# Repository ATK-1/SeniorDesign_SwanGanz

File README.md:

# Swan Ganz Interface

### Introduction

The contributors to this senior design project were Nathan DeLaRosa, Ashton Knecht, Jack Son, and Jerry Xia under the supervision of Dr. Jonathan Valvano.

This project aims to create a custom, low-cost interface for a Swan-Ganz heart catheter, bypassing the need for expensive cardiac output computers. The catheters intended to be interfaced are the *part number needed* produced by Edwards Lifescience. These catheters interface the *part number needed* pressure transducer, also made by Edwards Lifescience.

The project is split into three sections: the interface hardware, MSPM0 firmware, and the desktop application software. Details about each of these sections can be found in their distinct README files.

[Hardware README(In Progresss)](https://github.com/ATK-1/SeniorDesign_SwanGanz/blob/main/hardware/README.md)

[Firmware README(Requires Development)](https://github.com/ATK-1/SeniorDesign_SwanGanz/blob/main/firmware/README.md)

[Software README(Requires Development)](https://github.com/ATK-1/SeniorDesign_SwanGanz/blob/main/SwanGanzApp/README.md)

### Testing and Verification
*todo*

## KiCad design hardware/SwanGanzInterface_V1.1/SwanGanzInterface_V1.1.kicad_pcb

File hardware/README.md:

# Swan-Ganz Interface Hardware 
The Swan-Ganz Interface Hardware had the following requirements:
- One temperature channel for cardiac output calculation
- Two pressure transducer channels
- Discrete processor
- Intuitive user interface
- Uart to USB converter

The Swan-Ganz Interface has gone through two revisions in development. The first of these circuit boards aimed to have baseline functionality for testing, utilizing a launchpad processor for simplicity. The second revision aimed to refine the original with a discrete processor, a resistive touch screen, audio output, and an integrated UART-to-USB converter. This document will cover the hardware relevant to the second revision circuit board.

## Analog Interface Circuits
The heart of the hardware of this project is the analog interfaces for temperature and pressure. These interfaces are intended to interface the thermistor within the Swan-Ganz catheter and an external pressure transducer. These channels have very similar amplifier architectures; however, the interfaces to the transducers themselves have small differences. Each of the analog input stages was sampled by the analog to digital converters on the MSPM0+ microcontroller.

### Pressure Analog Interface
The Swan-Ganz Catheter does not natively have any pressure transducers. Instead, it has two ports that connect to the fluid in the catheter to external pressure transducers to measure pressure. Thus, to satisfy both pressure ports, two pressure channels must be included to service two independent transducers.

The independent pressure transducers are implemented with a strain gauge. This means that pressure is exerted on wires within the gauge, stretching and compressing them, changing their resistance. The model of the transducer's structure is shown below. The model consists of four variable resistors. Two of the resistors’ resistances are directly proportional to pressure, and two resistors are indirectly proportional. This results in a structure resembling a voltage divider, where a voltage is applied across the transducer; one output lead increases its output voltage with pressure, while the other decreases. 

With this architecture in mind, when a known voltage is applied across the gauge, an output voltage corresponding with pressure is produced across the V+ and V- nodes of the gauge. This signal is supplied to the instrumentation amplifier in the amplifier circuit at a very high gain to produce a clean pressure signal.

### Thermistor Analog Interface
The temperature channel hardware was created to interface with the thermistor embedded at the end of the Swan-Ganz catheter. This thermistor is intended to assist in the calculation of volumetric flow by analyzing its temperature over time; thus, it must translate temperature into a digital value. 

Within the thermistor, temperature and resistance are non-linear and inversely proportional. The thermistor has low resistance when the temperature is high and high resistance when the temperature is low. This relationship is shown by the graph below.

Thus, the thermistor can be placed into a resistor divider with a constant resistance value, producing an output voltage that correlates temperature to output voltage. Despite the relationship between resistance and temperature being non-linear, putting the thermistor in a resistor divider linearizes the output voltage as the relationship between resistance and voltage is non-linear in the divider itself. A second resistor divider with constant resistances is used to set a minimum resistance or a maximum temperature cutoff. The voltage across the variable and constant dividers is inserted into the instrumentation amplifier of the amplifier circuit to finish the temperature-to-voltage conversion. A diagram of the basic temperature circuit is shown below.

### Amplifier Stage
After converting the physical measurement to an analog voltage, the signal still requires analog filtering and amplification prior to being digitally sampled by the microcontroller. To do this, we must know some information about the characteristics of our signals and digital sampling for the design of our amplifier stage.

For our project, we decided to sample both the temperature and pressure signals at 200Hz. The typical resting heart rate in adults ranges from 60 to 100 beats per minute (BPM), which corresponds with a frequency of 1 to 1.67 Hz. During exercise, heart rate can increase up to 170 BPM, which is equivalent to 2.83 Hz. This means that the base frequency we would be investigating for pressure would be around 2 Hz. Despite this, we wanted to be able to view any additional high-frequency components of the heartbeat, as well as oversample our signal to increase the frequency before we started having aliasing in our digital signal. For the temperature component of our interface, we expected to receive even lower frequency signals, having frequencies of at most 10Hz; thus, the 200Hz sample rate was kept for consistency.

Because of the digital sample rate of 200Hz, any noise introduced to the system above 100 Hz cannot be distinguished from our desired signal, and cannot be
digitally filtered. Thus, to ensure that our resulting digital signals do not have any high-frequency noise, we created a 2-pole low-pass Butterworth filter set with a cut-off frequency of 75Hz. This allows us to pass the 20Hz signal frequencies while attenuating any high-frequency noise that is introduced from our environment. 

Amplification in this case is important as it determines the range and resolution of our
measurement. Our microcontroller, the MSPM0+, has 12-bit ADCs with an input voltage range of 0-3.3V. Therefore, to maximize the resolution of our signals, we must amplify the analog signals to make the largest desired analog signal equal to 3.3V. To do this, we have the amplification of the instrumentation amplifiers, tuned by a gain resistor, added by the 2-pole Butterworth filter, and an additional non-inverting amplifier for any additional required gain. To allow for both high resolution and high range, we sample with our ADCs both before and after the additional amplifier, allowing for a low-gain measurement that optimizes for range and a high-gain measurement for resolution. Below are pictures of the full analog input stages for the pressure and temperature interfaces.

## User Interface
The user interface for the Swan-Ganz Interface revolves around the 5” TFT display. This display is controlled by a discrete driver board, the Adafruit 1590. This driver board has SPI communication with the MSPM0+ processor. The driver board is required to boost the input voltage to the screen to 24V, as well as continuously refresh the TFT display. Drivers to communicate with the 1590 were provided by Adafruit and translated to C and to be compatible with the MSPM0+ by Nathan DeLaRosa.

The TFT screen supports a resistive touchscreen. This is provided by four screen outputs that interface with a discrete resistive touch screen controller IC, the TSC2046IPWR. This IC interfaces with the MSPM0+ through SPI and, upon its request, applies a voltage across the screen in the X and Y directions and samples its ADCs to determine the position of a touch to the screen. This information is then transmitted back to the MSPM0+ over another SPI channel for interpretation. The drivers to communicate with the TSC2046IPWR were written by Ashton Knecht.

In the case that issues arise with the resistive touch screen, five discrete hardware buttons are on the PCB as a backup user interface. The TFT is to provide a high-resolution, dynamic user interface able to display both measurement information and user instructions. This allows medical professionals to actively analyze measurement data while maintaining the correct procedure by following directions.

Since MSPM0+ does not natively support USB communication, a discrete UART-to-USB
converter is included to allow the microcontroller to communicate with a host computer running the desktop application. This IC is the FT232RNL, and supports a 3MHz baud rate, and has transmit and receive debug LEDs. Additionally, the manufacturer, FTDI, provides free drivers for Windows, Linux, and macOS.  

Lastly, support for an audio amplifier circuit was made to add a layer of user feedback; however, development on the core functionality and testing were prioritized, and so firmware functionality was not created. 

## Additional Elements of the PCB

### Reverse Polarity Protection

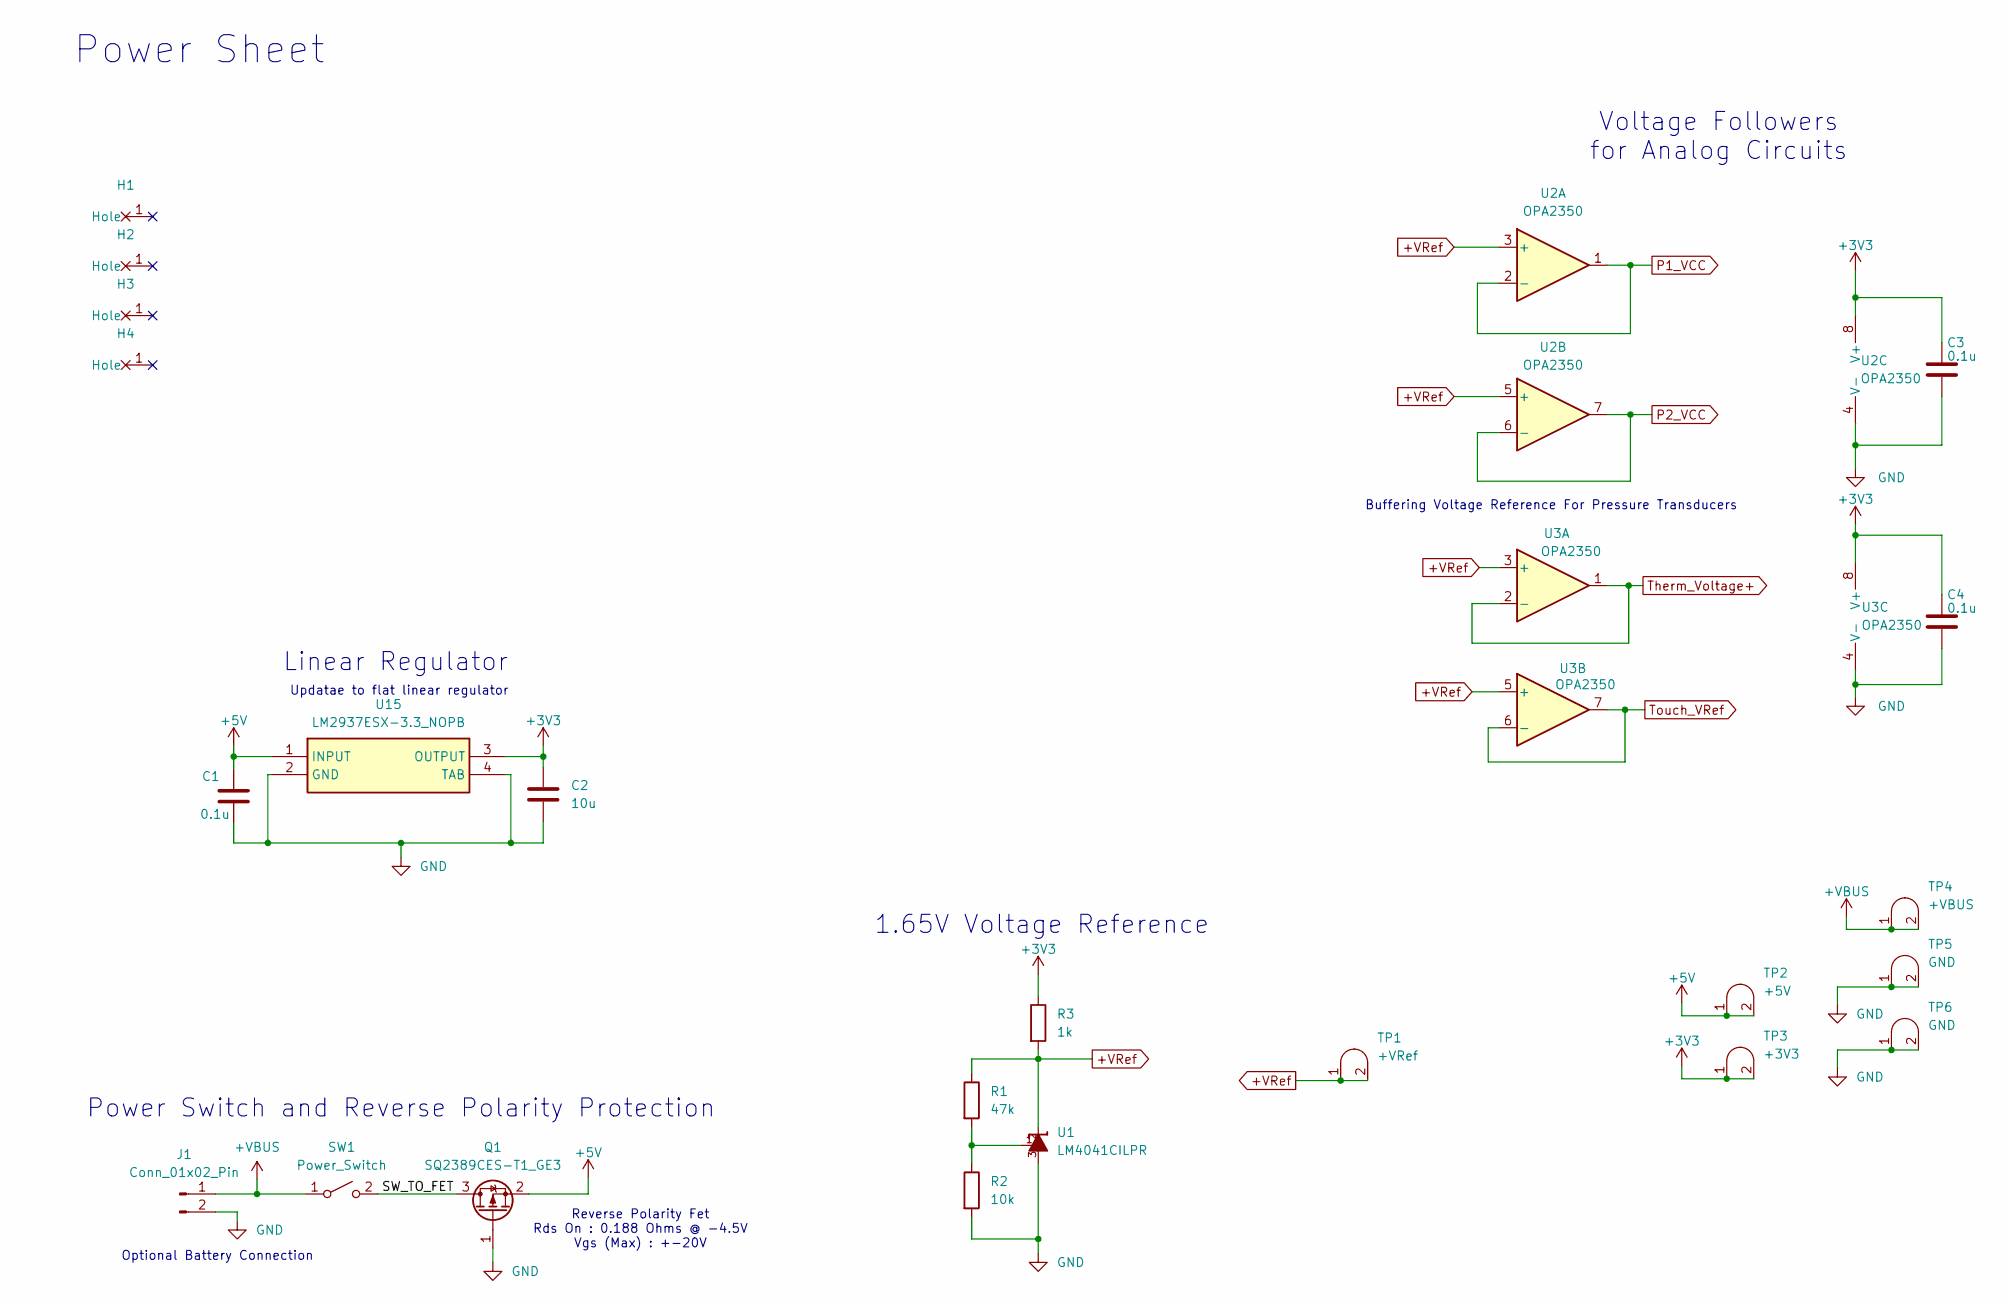
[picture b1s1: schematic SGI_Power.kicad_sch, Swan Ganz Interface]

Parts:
C1, C3, C4: 0.1u; C_0603_1608Metric
C2: 10u; C_1206_3216Metric
H1, H2, H3, H4: MountingHole_4_40
J1: Conn_01x02_Pin; PinHeader_1x02_P2.54mm_Vertical
Q1: SQ2389CES-T1_GE3; SOT-23
R1: 47k; R_0603_1608Metric
R2: 10k; R_0603_1608Metric
R3: 1k; R_0603_1608Metric
SW1: Power_Switch; SW-T3-1A-A-A3-S1
TP1: +VRef; Testpoint_1x02_P2.54mm
TP2: +5V; Testpoint_1x02_P2.54mm
TP3: +3V3; Testpoint_1x02_P2.54mm
TP4: +VBUS; Testpoint_1x02_P2.54mm
TP5, TP6: GND; Testpoint_1x02_P2.54mm
U1: LM4041CILPR; ti_LM4041CILPR
U2, U3: OPA2350; DIP-8_W7.62mm
U15: LM2937ESX-3.3_NOPB; Manufacturer_Part_Number LM2937ESX-3.3/NOPB; Mouser Part Number 926-LM2937ESX33NOPB

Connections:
+3V3: C2.1, C3.1, C4.1, R3.1, TP3.1 (A), TP3.2 (B), U2.8 (V+), U3.8 (V+), U15.3 (OUTPUT); also elsewhere on the board
+5V: C1.1, Q1.2 (S), TP2.1 (A), TP2.2 (B), U15.1 (INPUT); also elsewhere on the board
+VBUS: J1.1, SW1.1 (A), TP4.1 (A), TP4.2 (B); also elsewhere on the board
+VRef: R1.1, R3.2, TP1.1 (A), TP1.2 (B), U1.2, U2.3 (+), U2.5 (+), U3.3 (+), U3.5 (+)
/Power/SW_TO_FET: Q1.3 (D), SW1.2 (B)
GND: C1.2, C2.2, C3.2, C4.2, J1.2, Q1.1 (G), R2.2, TP5.1 (A), TP5.2 (B), TP6.1 (A), TP6.2 (B), U1.3, U2.4 (V-), U3.4 (V-), U15.2 (GND), U15.4 (TAB); also elsewhere on the board
unnamed: R1.2, R2.1, U1.1
P1_VCC: U2.1, U2.2 (-); also elsewhere on the board
P2_VCC: U2.6 (-), U2.7; also elsewhere on the board
Therm_Voltage+: U3.1, U3.2 (-); also elsewhere on the board
Touch_VRef: U3.6 (-), U3.7; also elsewhere on the board

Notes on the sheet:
Buffering Voltage Reference For Pressure Transducers
Power Switch and Reverse Polarity Protection
Power Sheet
Updatae to flat linear regulator
Reverse Polarity Fet Rds On : 0.188 Ohms @ -4.5V Vgs (Max) : +-20V
Voltage Followers for Analog Circuits
Linear Regulator
1.65V Voltage Reference
Optional Battery Connection

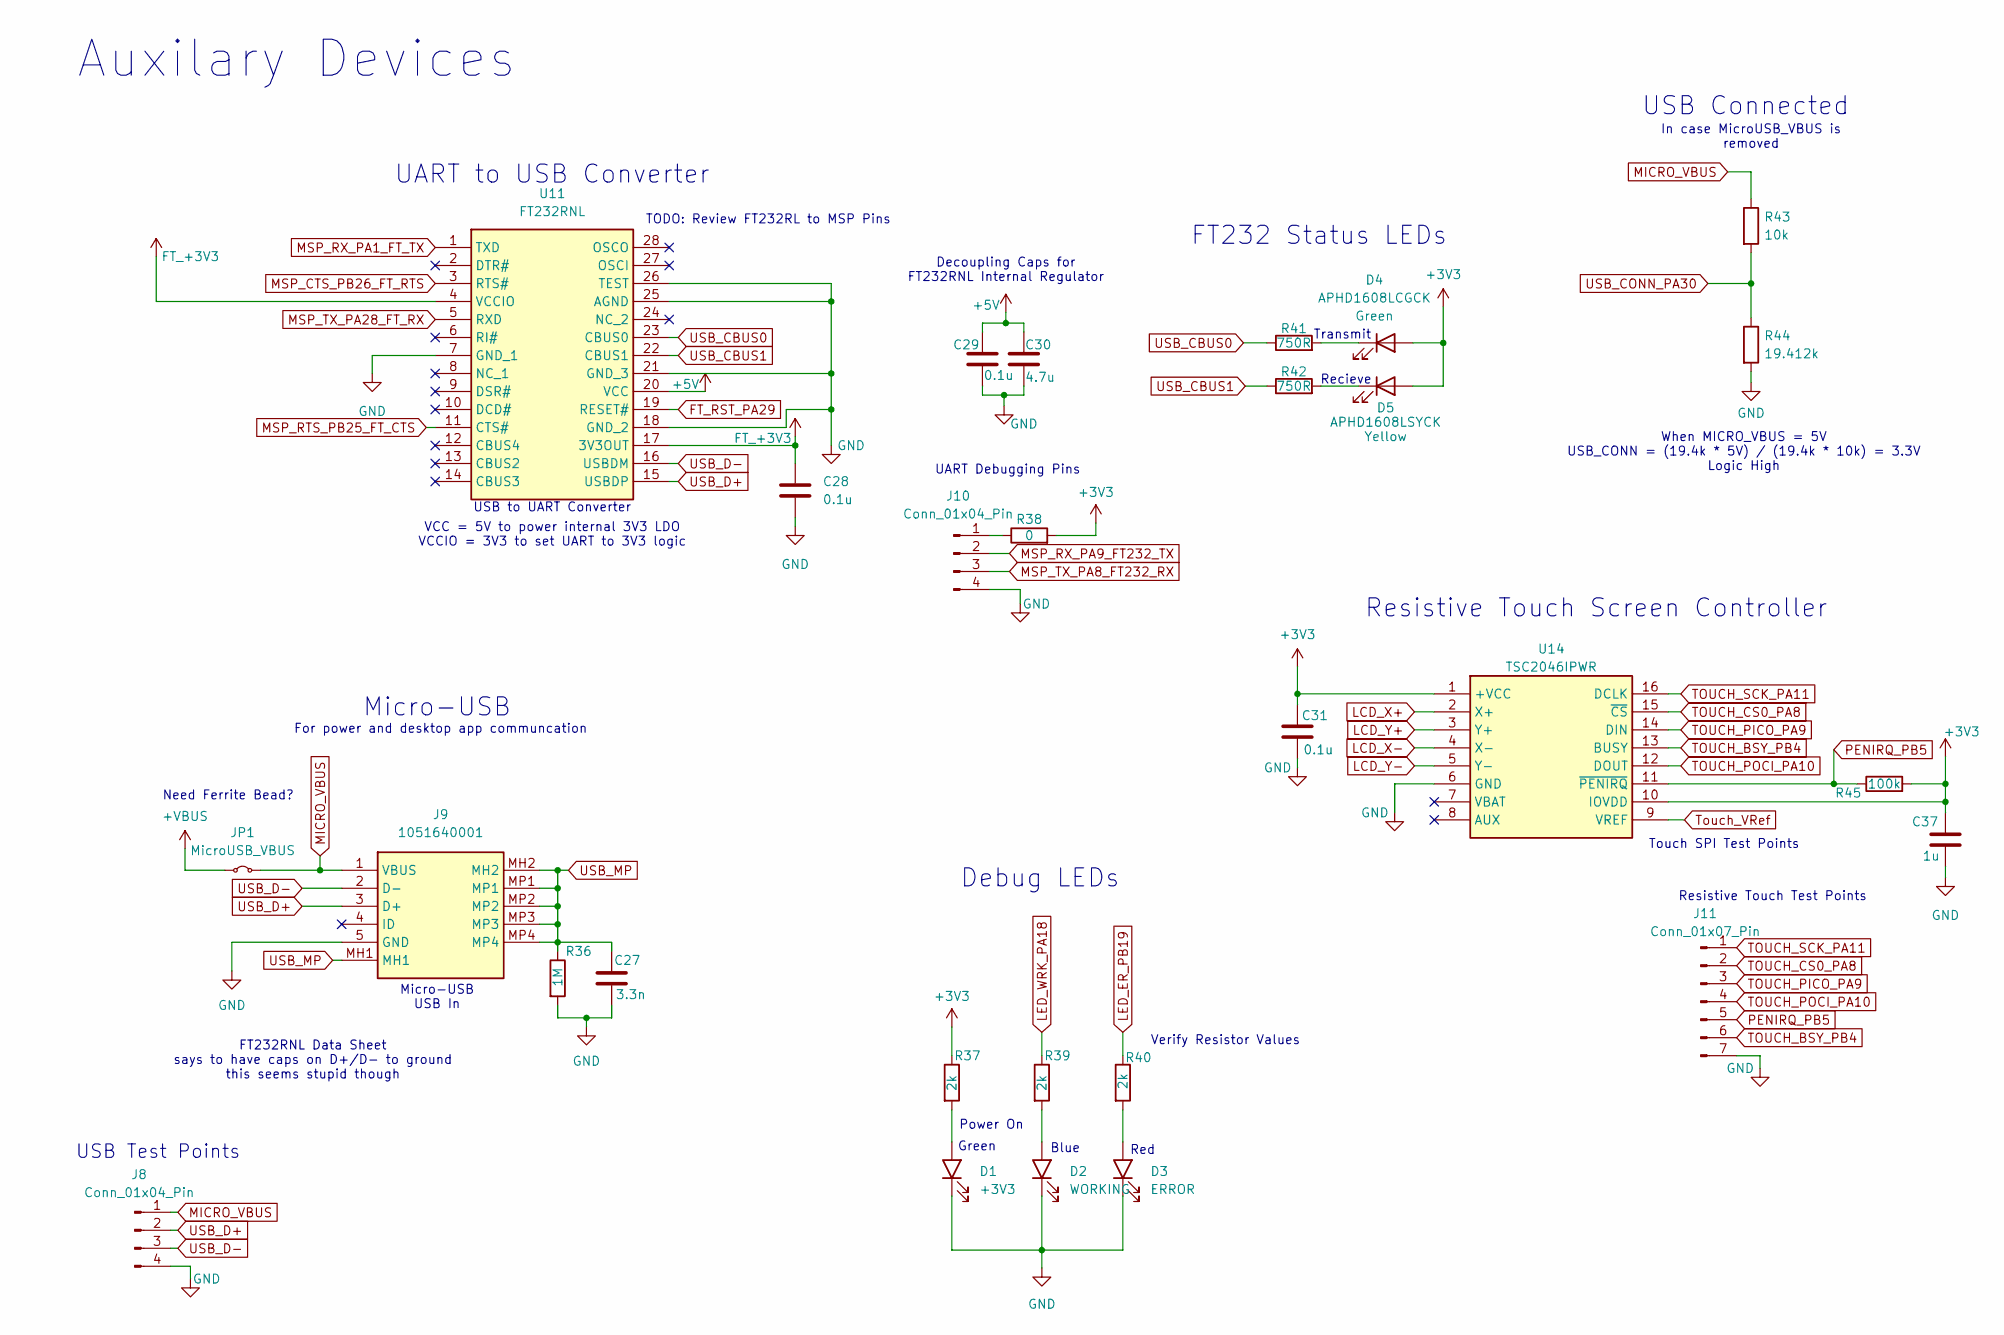
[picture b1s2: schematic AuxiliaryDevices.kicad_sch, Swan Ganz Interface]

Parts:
C27: 3.3n; C_0603_1608Metric
C28, C29, C31: 0.1u; C_0603_1608Metric
C30: 4.7u; C_0805_2012Metric
C37: 1u; C_0603_1608Metric
D1: +3V3; LED_D5.0mm
D2: WORKING; LED_D5.0mm
D3: ERROR; LED_D5.0mm
D4: APHD1608LCGCK; D_0603_1608Metric; Forward Voltage 1.9V
D5: APHD1608LSYCK; D_0603_1608Metric; Forward Voltage 1.85V
J8, J10: Conn_01x04_Pin; PinHeader_1x04_P2.54mm_Vertical
J9: 1051640001; Manufacturer_Part_Number 1051640001; Mouser Part Number N/A
J11: Conn_01x07_Pin; PinHeader_1x07_P2.54mm_Vertical
JP1: MicroUSB_VBUS; PinHeader_1x02_P2.54mm_Vertical
R36: 1M; R_0603_1608Metric
R37, R39, R40: 2k; R_0603_1608Metric
R38: 0; R_0603_1608Metric
R41, R42: 750R; R_0603_1608Metric
R43: 10k; R_0603_1608Metric
R44: 19.412k; R_0603_1608Metric
R45: 100k; R_0603_1608Metric
U11: FT232RNL; FT232RL; Manufacturer_Part_Number FT232RNL
U14: TSC2046IPWR; SOP65P640X120-16N; Manufacturer_Part_Number TSC2046IPWR; Mouser Part Number 595-TSC2046IPWR

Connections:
+3V3: C31.1, C37.1, D4.2 (A), D5.2 (A), R37.1, R38.2, R45.2, U14.1 (+VCC), U14.10 (IOVDD); also elsewhere on the board
+5V: C29.2, C30.2, U11.20 (VCC); also elsewhere on the board
+VBUS: JP1.1 (A); also elsewhere on the board
FT_+3V3: C28.1, U11.4 (VCCIO), U11.17 (3V3OUT)
FT_RST_PA29: U11.19 (RESET#); also elsewhere on the board
GND: C27.2, C28.2, C29.1, C30.1, C31.2, C37.2, D1.1 (K), D2.1 (K), D3.1 (K), J8.4, J9.5 (GND), J10.4, J11.7, R36.2, R44.2, U11.7 (GND_1), U11.18 (GND_2), U11.21 (GND_3), U11.25 (AGND), U11.26 (TEST), U14.6 (GND); also elsewhere on the board
LCD_X+: U14.2 (X+); also elsewhere on the board
LCD_X-: U14.4 (X-); also elsewhere on the board
LCD_Y+: U14.3 (Y+); also elsewhere on the board
LCD_Y-: U14.5 (Y-); also elsewhere on the board
LED_ER_PB19: R40.1; also elsewhere on the board
LED_WRK_PA18: R39.1; also elsewhere on the board
MICRO_VBUS: J8.1, J9.1 (VBUS), JP1.2 (B), R43.1
MSP_CTS_PB26_FT_RTS: U11.3 (RTS#); also elsewhere on the board
MSP_RTS_PB25_FT_CTS: U11.11 (CTS#); also elsewhere on the board
MSP_RX_PA1_FT_TX: U11.1 (TXD); also elsewhere on the board
MSP_RX_PA9_FT232_TX: J10.2
MSP_TX_PA8_FT232_RX: J10.3
MSP_TX_PA28_FT_RX: U11.5 (RXD); also elsewhere on the board
unnamed: D1.2 (A), R37.2
unnamed: D2.2 (A), R39.2
unnamed: D3.2 (A), R40.2
unnamed: D4.1 (K), R41.2
unnamed: D5.1 (K), R42.2
unnamed: J10.1, R38.1
PENIRQ_PB5: J11.5, R45.1, U14.11 (~PENIRQ); also elsewhere on the board
TOUCH_BSY_PB4: J11.6, U14.13 (BUSY); also elsewhere on the board
TOUCH_CS0_PA8: J11.2, U14.15 (~CS); also elsewhere on the board
TOUCH_PICO_PA9: J11.3, U14.14 (DIN); also elsewhere on the board
TOUCH_POCI_PA10: J11.4, U14.12 (DOUT); also elsewhere on the board
TOUCH_SCK_PA11: J11.1, U14.16 (DCLK); also elsewhere on the board
Touch_VRef: U14.9 (VREF); also elsewhere on the board
USB_CBUS0: R41.1, U11.23 (CBUS0)
USB_CBUS1: R42.1, U11.22 (CBUS1)
USB_CONN_PA30: R43.2, R44.1; also elsewhere on the board
USB_D+: J8.2, J9.3 (D+), U11.15 (USBDP)
USB_D-: J8.3, J9.2 (D-), U11.16 (USBDM)
USB_MP: C27.1, J9.MH1, J9.MH2, J9.MP1, J9.MP2, J9.MP3, J9.MP4, R36.1

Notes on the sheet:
In case MicroUSB_VBUS is removed
TODO: Review FT232RL to MSP Pins
USB Test Points
Need Ferrite Bead?
UART Debugging Pins
USB In
FT232RNL Data Sheet says to have caps on D+/D- to ground this seems stupid though
Green
USB Connected
Verify Resistor Values
Resistive Touch Screen Controller
Blue
VCC = 5V to power internal 3V3 LDO VCCIO = 3V3 to set UART to 3V3 logic
Debug LEDs
Auxilary Devices
Transmit
USB to UART Converter
Micro-USB
Decoupling Caps for FT232RNL Internal Regulator
Resistive Touch Test Points
When MICRO_VBUS = 5V USB_CONN = (19.4k * 5V) / (19.4k * 10k) = 3.3V Logic High
Power On
UART to USB Converter
Recieve
Touch SPI Test Points
For power and desktop app communcation
FT232 Status LEDs
Micro-USB
Red

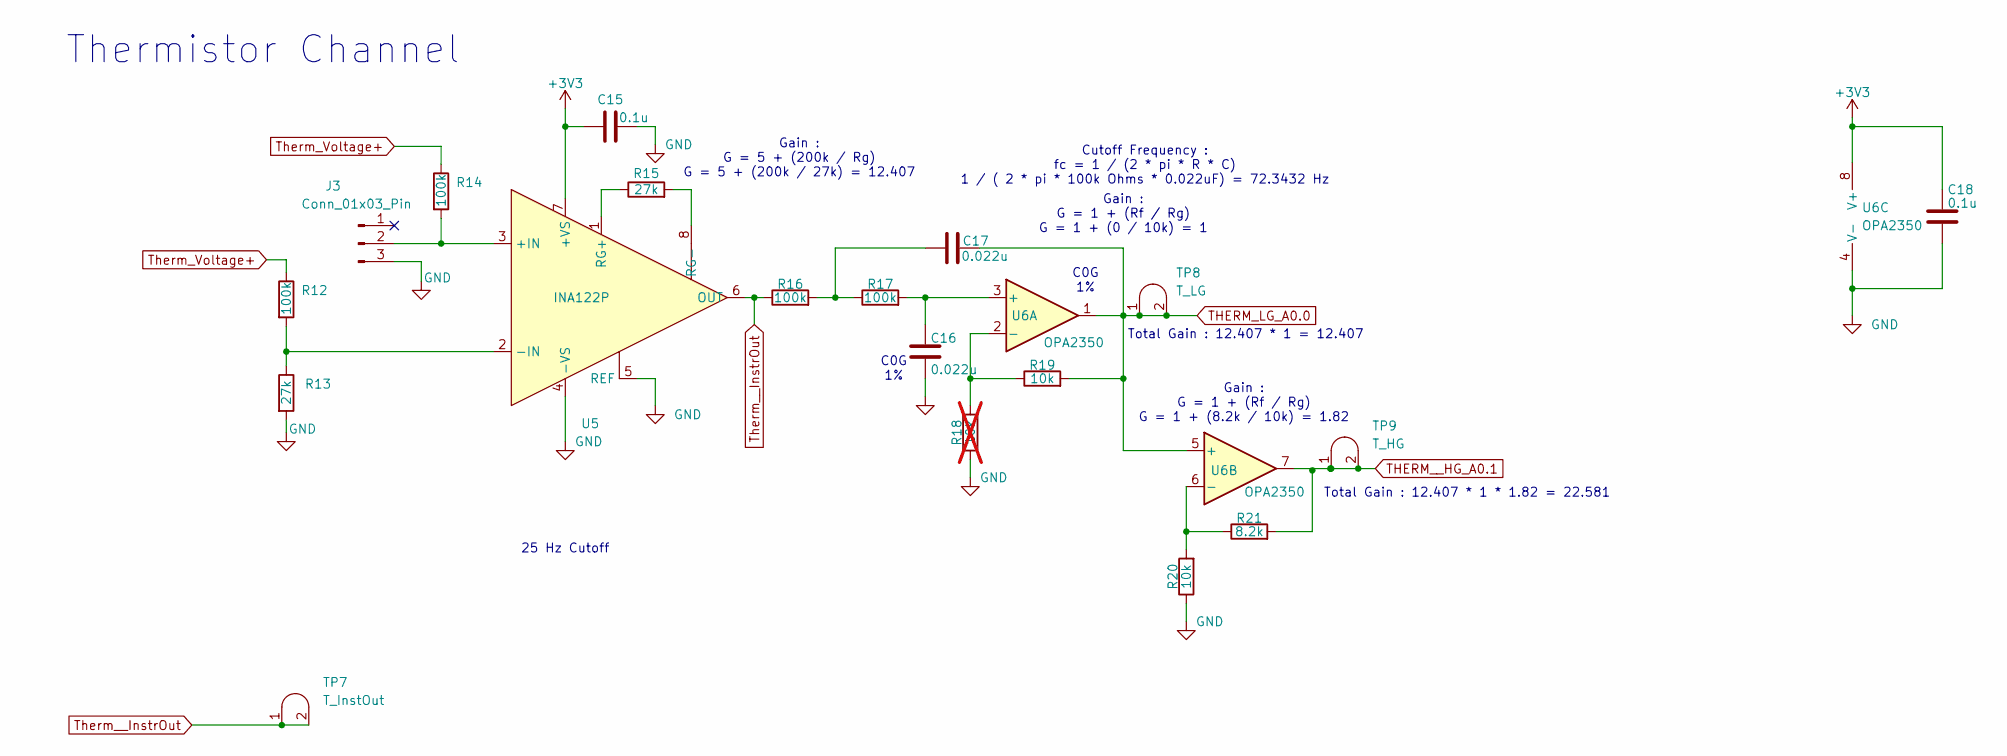
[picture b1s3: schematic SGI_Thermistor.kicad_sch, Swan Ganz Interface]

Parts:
C15, C18: 0.1u; C_0603_1608Metric
C16, C17: 0.022u; C_0805_2012Metric
J3: Conn_01x03_Pin; PinHeader_1x03_P2.54mm_Vertical
R12, R14, R16, R17: 100k; R_0603_1608Metric
R13, R15: 27k; R_0603_1608Metric
R18: 10k; R_0603_1608Metric; not fitted
R19, R20: 10k; R_0603_1608Metric
R21: 8.2k; R_0603_1608Metric
TP7: T_InstOut; Testpoint_1x02_P2.54mm
TP8: T_LG; Testpoint_1x02_P2.54mm
TP9: T_HG; Testpoint_1x02_P2.54mm
U5: INA122P; DIP-8_W7.62mm_LongPads
U6: OPA2350; DIP-8_W7.62mm

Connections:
+3V3: C15.2, C18.1, U5.7 (+VS), U6.8 (V+); also elsewhere on the board
GND: C15.1, C16.2, C18.2, J3.3, R13.2, R18.1, R20.1, U5.4 (-VS), U5.5 (REF), U6.4 (V-); also elsewhere on the board
unnamed: C17.1, R16.2, R17.1
unnamed: J3.2, R14.2, U5.3 (+IN)
unnamed: R12.2, R13.1, U5.2 (-IN)
unnamed: R15.1, U5.1 (RG+)
unnamed: R15.2, U5.8 (RG-)
unnamed: C16.1, R17.2, U6.3 (+)
unnamed: R18.2, R19.1, U6.2 (-)
unnamed: R20.2, R21.1, U6.6 (-)
THERM_LG_A0.0: C17.2, R19.2, TP8.1 (A), TP8.2 (B), U6.1, U6.5 (+); also elsewhere on the board
THERM__HG_A0.1: R21.2, TP9.1 (A), TP9.2 (B), U6.7; also elsewhere on the board
Therm_Voltage+: R12.1, R14.1; also elsewhere on the board
Therm__InstrOut: R16.1, TP7.1 (A), TP7.2 (B), U5.6 (OUT)

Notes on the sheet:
Gain : G = 5 + (200k / Rg) G = 5 + (200k / 27k) = 12.407
Total Gain : 12.407 * 1 = 12.407
C0G 1%
Total Gain : 12.407 * 1 * 1.82 = 22.581
25 Hz Cutoff
Cutoff Frequency : fc = 1 / (2 * pi * R * C) 1 / ( 2 * pi * 100k Ohms * 0.022uF) = 72.3432 Hz
Gain : G = 1 + (Rf / Rg) G = 1 + (0 / 10k) = 1
Gain : G = 1 + (Rf / Rg) G = 1 + (8.2k / 10k) = 1.82
Thermistor Channel

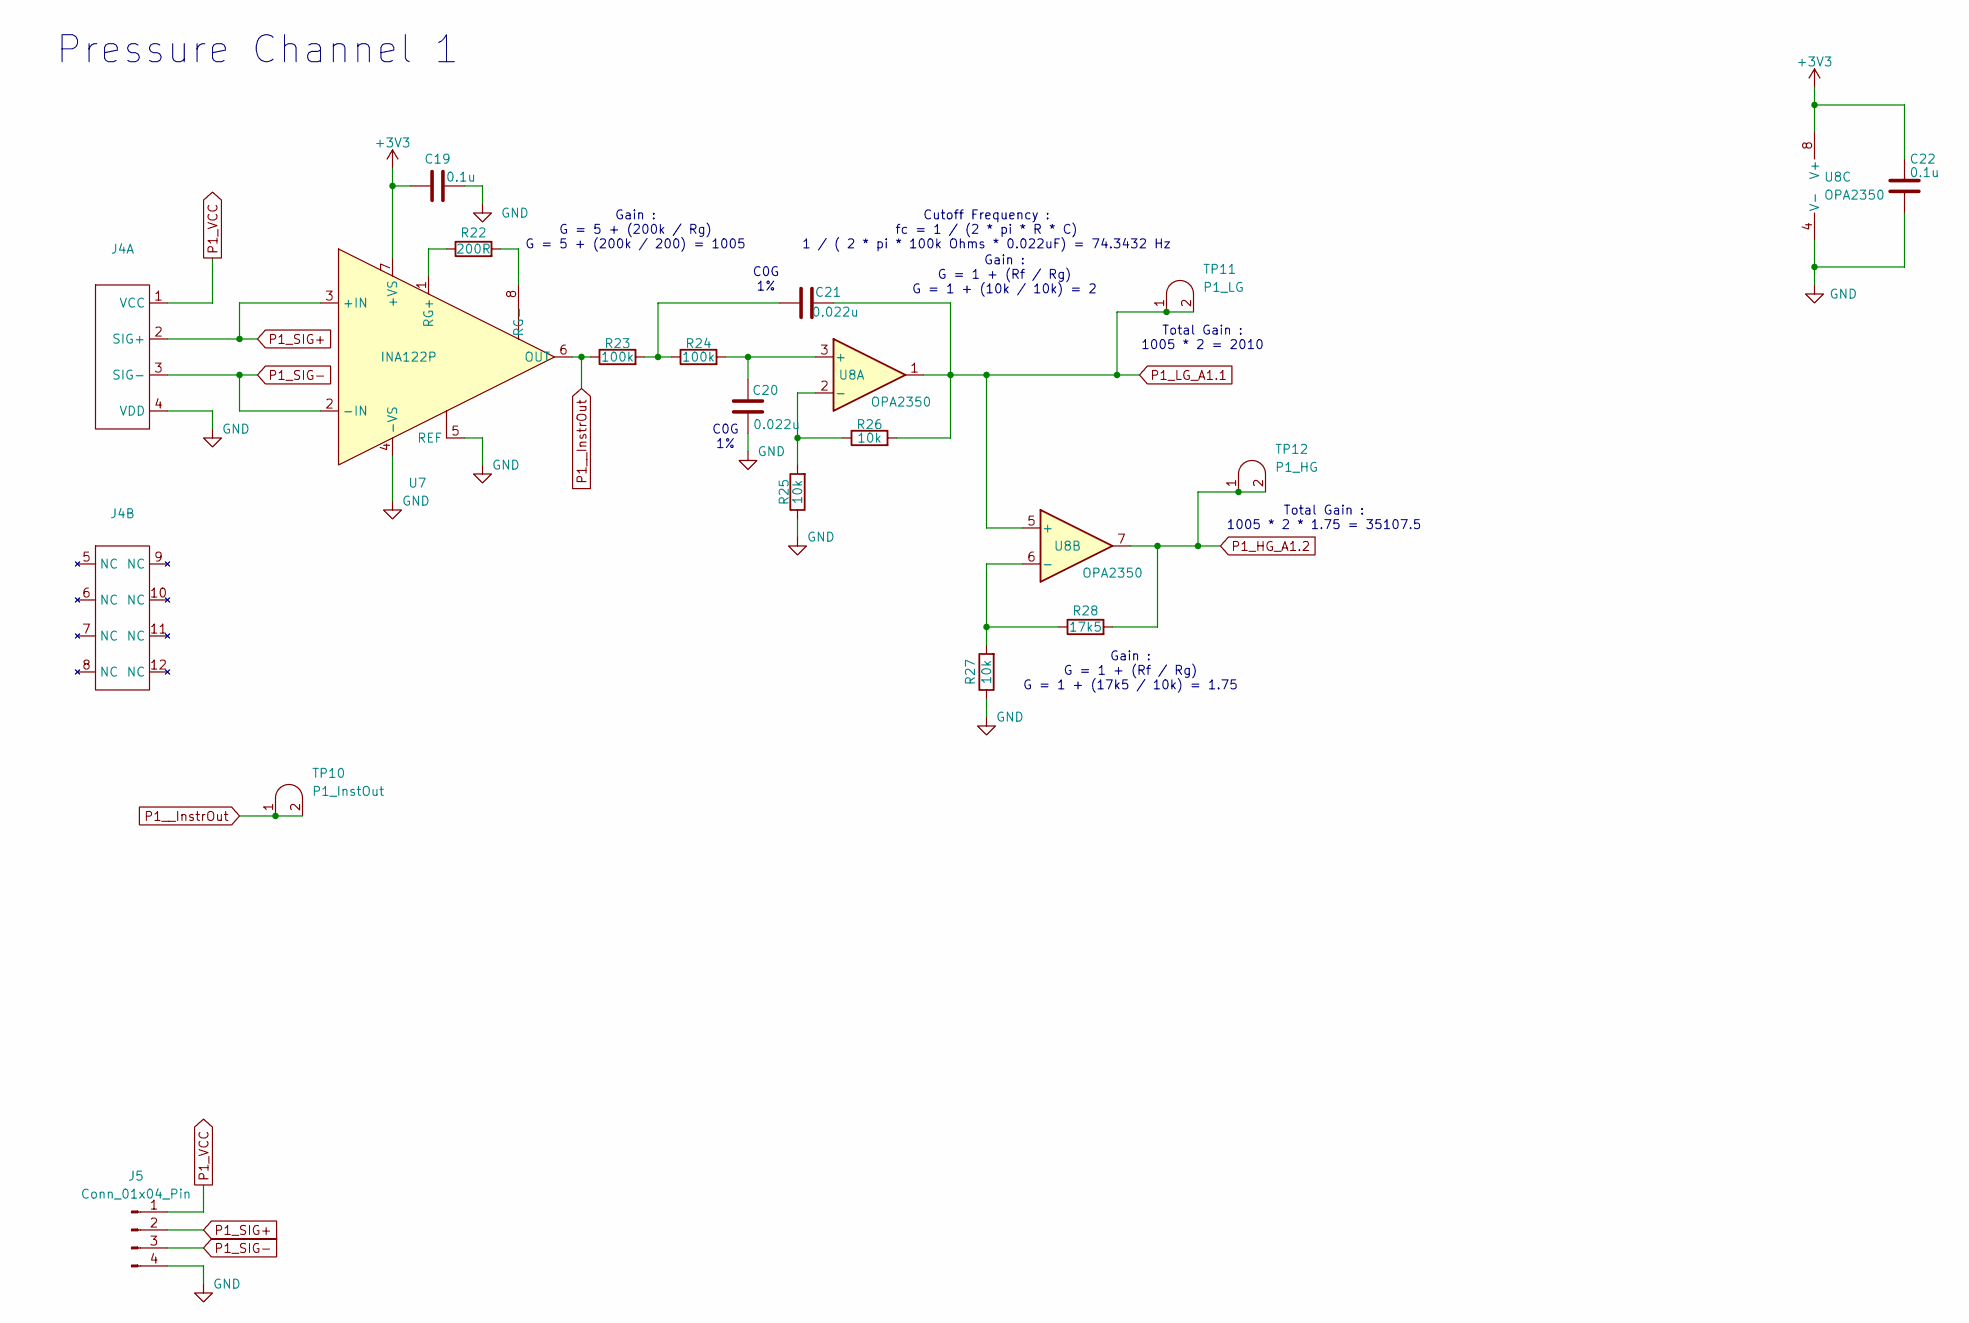
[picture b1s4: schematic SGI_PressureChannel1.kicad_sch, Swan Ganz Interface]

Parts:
C19, C22: 0.1u; C_0603_1608Metric
C20, C21: 0.022u; C_0603_1608Metric
J4: Pressure_Connector_1.1
J5: Conn_01x04_Pin; PinSocket_1x04_P2.54mm_Vertical
R22: 200R; R_0603_1608Metric
R23, R24: 100k; R_0603_1608Metric
R25, R26, R27: 10k; R_0603_1608Metric
R28: 17k5; R_0603_1608Metric
TP10: P1_InstOut; Testpoint_1x02_P2.54mm
TP11: P1_LG; Testpoint_1x02_P2.54mm
TP12: P1_HG; Testpoint_1x02_P2.54mm
U7: INA122P; DIP-8_W7.62mm_LongPads
U8: OPA2350; DIP-8_W7.62mm

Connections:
+3V3: C19.2, C22.1, U7.7 (+VS), U8.8 (V+); also elsewhere on the board
GND: C19.1, C20.2, C22.2, J4.4 (VDD), J5.4, R25.1, R27.1, U7.4 (-VS), U7.5 (REF), U8.4 (V-); also elsewhere on the board
unnamed: C21.1, R23.2, R24.1
unnamed: R22.1, U7.1 (RG+)
unnamed: R22.2, U7.8 (RG-)
unnamed: C20.1, R24.2, U8.3 (+)
unnamed: R25.2, R26.1, U8.2 (-)
unnamed: R27.2, R28.1, U8.6 (-)
P1_HG_A1.2: R28.2, TP12.1 (A), TP12.2 (B), U8.7; also elsewhere on the board
P1_LG_A1.1: C21.2, R26.2, TP11.1 (A), TP11.2 (B), U8.1, U8.5 (+); also elsewhere on the board
P1_SIG+: J4.2 (SIG+), J5.2, U7.3 (+IN)
P1_SIG-: J4.3 (SIG-), J5.3, U7.2 (-IN)
P1_VCC: J4.1 (VCC), J5.1; also elsewhere on the board
P1__InstrOut: R23.1, TP10.1 (A), TP10.2 (B), U7.6 (OUT)

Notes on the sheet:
Gain : G = 1 + (Rf / Rg) G = 1 + (17k5 / 10k) = 1.75
Total Gain : 1005 * 2 = 2010
Gain : G = 1 + (Rf / Rg) G = 1 + (10k / 10k) = 2
Cutoff Frequency : fc = 1 / (2 * pi * R * C) 1 / ( 2 * pi * 100k Ohms * 0.022uF) = 74.3432 Hz
Gain : G = 5 + (200k / Rg) G = 5 + (200k / 200) = 1005
Pressure Channel 1
Total Gain : 1005 * 2 * 1.75 = 35107.5
C0G 1%

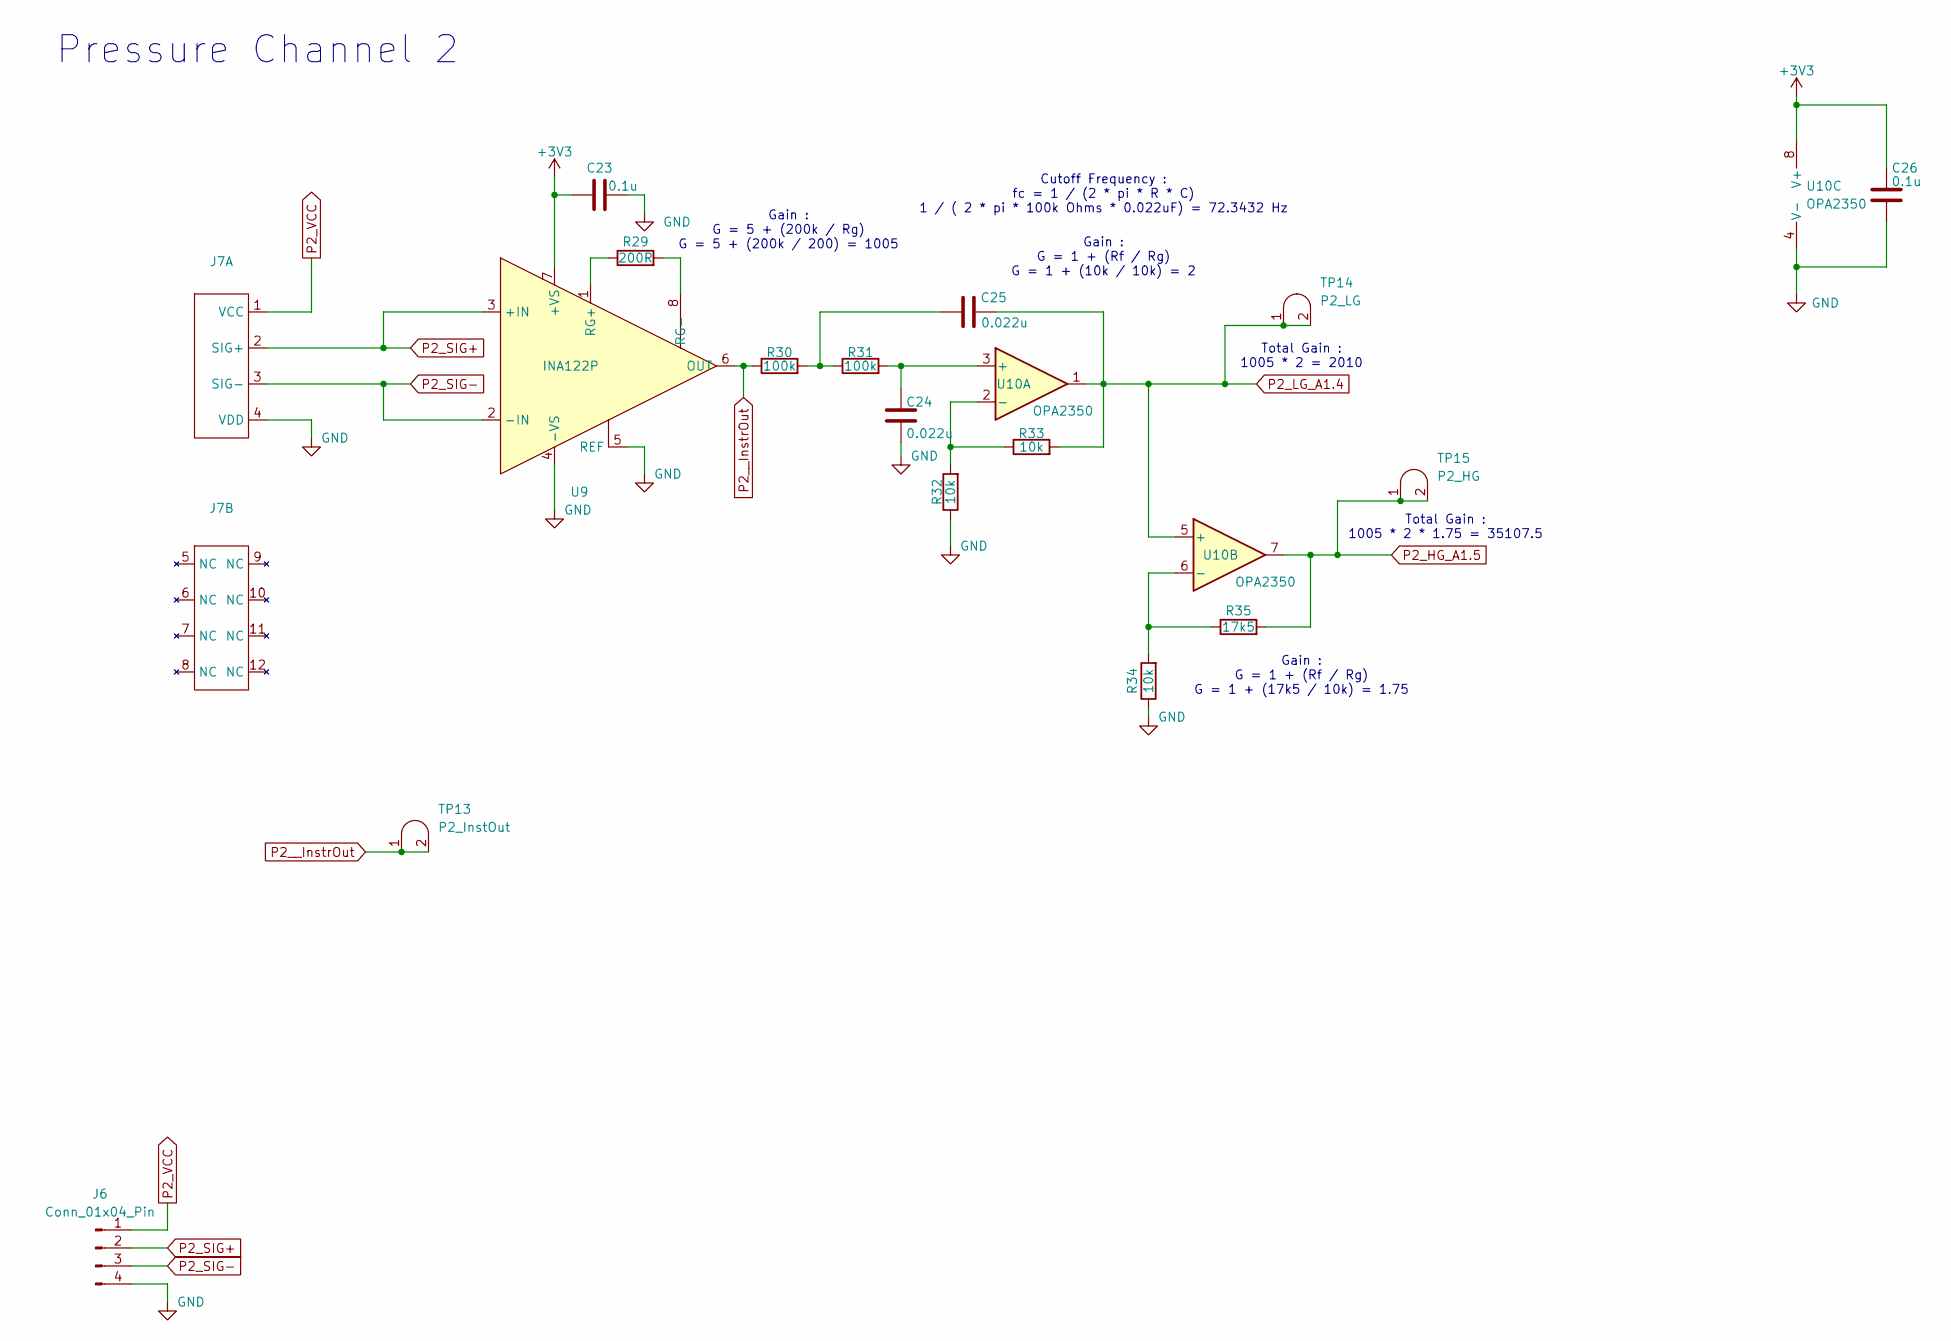
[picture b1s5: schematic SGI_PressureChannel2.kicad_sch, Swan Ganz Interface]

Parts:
C23, C26: 0.1u; C_0603_1608Metric
C24: 0.022u; C_0805_2012Metric
C25: 0.022u; C_0603_1608Metric
J6: Conn_01x04_Pin; PinSocket_1x04_P2.54mm_Vertical
J7: Pressure_Connector_1.1
R29: 200R; R_0603_1608Metric
R30, R31: 100k; R_0603_1608Metric
R32, R33, R34: 10k; R_0603_1608Metric
R35: 17k5; R_0603_1608Metric
TP13: P2_InstOut; Testpoint_1x02_P2.54mm
TP14: P2_LG; Testpoint_1x02_P2.54mm
TP15: P2_HG; Testpoint_1x02_P2.54mm
U9: INA122P; DIP-8_W7.62mm_LongPads
U10: OPA2350; DIP-8_W7.62mm

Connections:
+3V3: C23.2, C26.1, U9.7 (+VS), U10.8 (V+); also elsewhere on the board
GND: C23.1, C24.2, C26.2, J6.4, J7.4 (VDD), R32.1, R34.1, U9.4 (-VS), U9.5 (REF), U10.4 (V-); also elsewhere on the board
unnamed: C25.1, R30.2, R31.1
unnamed: R29.1, U9.1 (RG+)
unnamed: R29.2, U9.8 (RG-)
unnamed: C24.1, R31.2, U10.3 (+)
unnamed: R32.2, R33.1, U10.2 (-)
unnamed: R34.2, R35.1, U10.6 (-)
P2_HG_A1.5: R35.2, TP15.1 (A), TP15.2 (B), U10.7; also elsewhere on the board
P2_LG_A1.4: C25.2, R33.2, TP14.1 (A), TP14.2 (B), U10.1, U10.5 (+); also elsewhere on the board
P2_SIG+: J6.2, J7.2 (SIG+), U9.3 (+IN)
P2_SIG-: J6.3, J7.3 (SIG-), U9.2 (-IN)
P2_VCC: J6.1, J7.1 (VCC); also elsewhere on the board
P2__InstrOut: R30.1, TP13.1 (A), TP13.2 (B), U9.6 (OUT)

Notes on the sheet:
Gain : G = 1 + (Rf / Rg) G = 1 + (17k5 / 10k) = 1.75
Cutoff Frequency : fc = 1 / (2 * pi * R * C) 1 / ( 2 * pi * 100k Ohms * 0.022uF) = 72.3432 Hz
Total Gain : 1005 * 2 * 1.75 = 35107.5
Gain : G = 5 + (200k / Rg) G = 5 + (200k / 200) = 1005
Pressure Channel 2
Gain : G = 1 + (Rf / Rg) G = 1 + (10k / 10k) = 2
Total Gain : 1005 * 2 = 2010
